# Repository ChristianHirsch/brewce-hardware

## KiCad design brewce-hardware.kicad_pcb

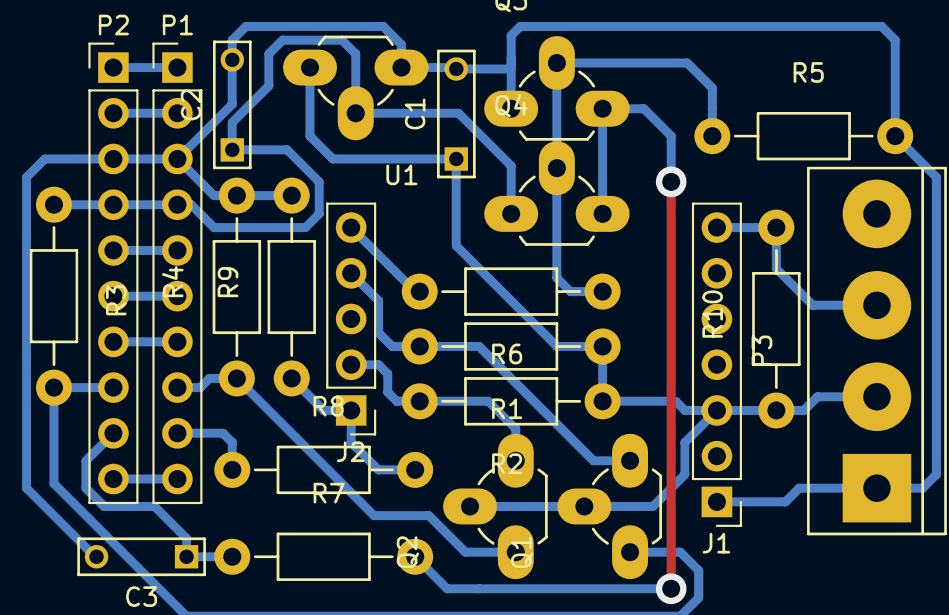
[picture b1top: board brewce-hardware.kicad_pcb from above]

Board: 2 copper layers, 23 parts (0 on the bottom side), 20 nets.

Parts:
C1, C2, C3: 1u; C_Rect_L7_W2_P5
J1: CONN_01X07; Socket_Strip_Straight_1x07_Pitch2.54mm
J2: CONN_01X05; Socket_Strip_Straight_1x05_Pitch2.54mm
P1: CONN_I; Pin_Header_Straight_1x10_Pitch2.54mm
P2: CONN_O; Pin_Header_Straight_1x10_Pitch2.54mm
P3: CONN_01X04; bornier4
Q1, Q2, Q3: 2N7000; TO-92_Rugged
Q4: Q_PMOS_DGS; TO-92_Rugged
R1, R2, R3, R4, R5: 10k; Resistor_Horizontal_RM10mm
R6: 100; Resistor_Horizontal_RM10mm
R7: 100k; Resistor_Horizontal_RM10mm
R8, R9: R; Resistor_Horizontal_RM10mm
R10: 4.7k; Resistor_Horizontal_RM10mm
U1: MCP1700-3302E_TO92; TO-92_Rugged

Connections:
/1: P1.1, P2.1
/2: P1.2, P2.2
/5: P1.5, P2.5
/6: P1.6, P2.6
/7: P1.7, P2.7
/10: P1.10, P2.10
/IO_I: P1.8, Q2.1, R4.1
/IO_O: P2.8, Q1.1, R3.2
/Power_I: P1.9, R8.1
/Power_O: C3.1, P2.9, R7.1
/Simblee/GPIO1: J1.7, P3.3, R10.2
/Simblee/GPIO2: J2.5, R6.2
/Simblee/GPIO3: J2.4, Q1.3, R1.2
/Simblee/GPIO5: J2.2, Q2.3, R2.2
/Simblee/GPIO6: J2.1, R8.2, R9.1
GND: C1.2, C2.2, C3.2, J1.1, P1.3, P2.3, P3.1, Q3.1, R4.2, R5.2, R9.2, U1.1
unnamed: Q3.2, Q4.2, R5.1, R6.1
unnamed: Q3.3, Q4.3, R7.2
VAA: C2.1, P1.4, P2.4, Q4.1, R3.1, U1.2
VDD: C1.1, J1.3, P3.2, Q1.2, Q2.2, R1.1, R2.1, R10.1, U1.3

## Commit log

2017-11-16 update schematics & PCB
2017-11-17 fix some problems in the schematics
    - IO input read, use pull down instead of pull up
    - PWM output to get all the values from 0 .. VAA for power output
2017-11-29 improve schematics, update pcb
2017-12-07 fix pwm level shifter
